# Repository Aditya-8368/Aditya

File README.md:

# stage-1------------------------------------------------------------<br>

# problem-1 : Design a schematic of circuit controlling a servo motor using a potentiometer. Also Simulate the circuit on tinkercad

link to tinker cad for my project of stage-1 (https://www.tinkercad.com/things/lVUwzbY1CdB-stage-1)

code of Arduino:

#include <Servo.h>

int val = 0;

int servo = 0;

int outval = 0;

Servo servo_9;

void setup()
{
  pinMode(A1, INPUT);
  servo_9.attach(9, 500, 2500);
  pinMode(LED_BUILTIN, OUTPUT);
}

void loop()
{
  val = analogRead(A1);
  outval = map(val, 0, 1023, 0, 180);
  servo_9.write(outval);

  digitalWrite(LED_BUILTIN, HIGH);
  delay(10); // Delay a little bit to improve simulation performance
}

# stage-2------------------------------------------------------------<br>

# problem-1 : Controlling LED intensity using PWM registers directly. (without using analogWrite/digitalWrite function)

this is a link for my tinkercad file for stage-2 problem-1 (https://www.tinkercad.com/things/dcMnIvQHpTa-magnificent-amberis)

Arduino code :

// C++ code

const int ledPin = 9;

void setup() {
  
  pinMode(ledPin, OUTPUT);

  TCCR1A |= (1 << WGM11) | (1 << COM1A1);
  TCCR1B |= (1 << WGM12) | (1 << WGM13) | (1 << CS10);

  OCR1A = 255;

  OCR1B = 0;
}

void loop() {
  
  for (int brightness = 0; brightness <= 255; brightness++) {
    OCR1B = brightness;
    delay(10);
  }

  for (int brightness = 255; brightness >= 0; brightness--) {
    OCR1B = brightness;
    delay(10);
  }
}

# problem-2 : Sweep a servo without using the Servo library controlled with IR remote. (Press 1 for right sweep ie from 0 to 180 degree and 2 for reverse)

this is a link for my tinkercad file for stage-2 problem-2 (https://www.tinkercad.com/things/60p1n9k2j1E-sizzling-blad)

Arduino code :
# NOTE : This code is not working in tinkercad dut to "IRRemote configuration of buttons" but compilation is going well and it will run on another remote or hardware

#include <IRremote.h>

#define IR_PIN 11 
#define SERVO_PIN 9

IRrecv irrecv(IR_PIN);
decode_results results;

int servoPos = 0;

void setup() {
  pinMode(SERVO_PIN, OUTPUT);
  irrecv.enableIRIn();
}

void loop() {
  if (irrecv.decode(&results)) {
    if (results.value == 0xFF30CF) { 
      sweepServo(0, 180, 1);
    } else if (results.value == 0xFF18E7) { 
      sweepServo(180, 0, -1);
    }
    irrecv.resume();
  }
}

void sweepServo(int from, int to, int step) {
  for (int i = from; i != to; i += step) {
    servoPos = i;
    updateServo();
    delay(15);
  }
}

void updateServo() {
  
  int pulseWidth = map(servoPos, 0, 180, 500, 2500);
  
  digitalWrite(SERVO_PIN, HIGH);
  delayMicroseconds(pulseWidth);
  digitalWrite(SERVO_PIN, LOW);
}

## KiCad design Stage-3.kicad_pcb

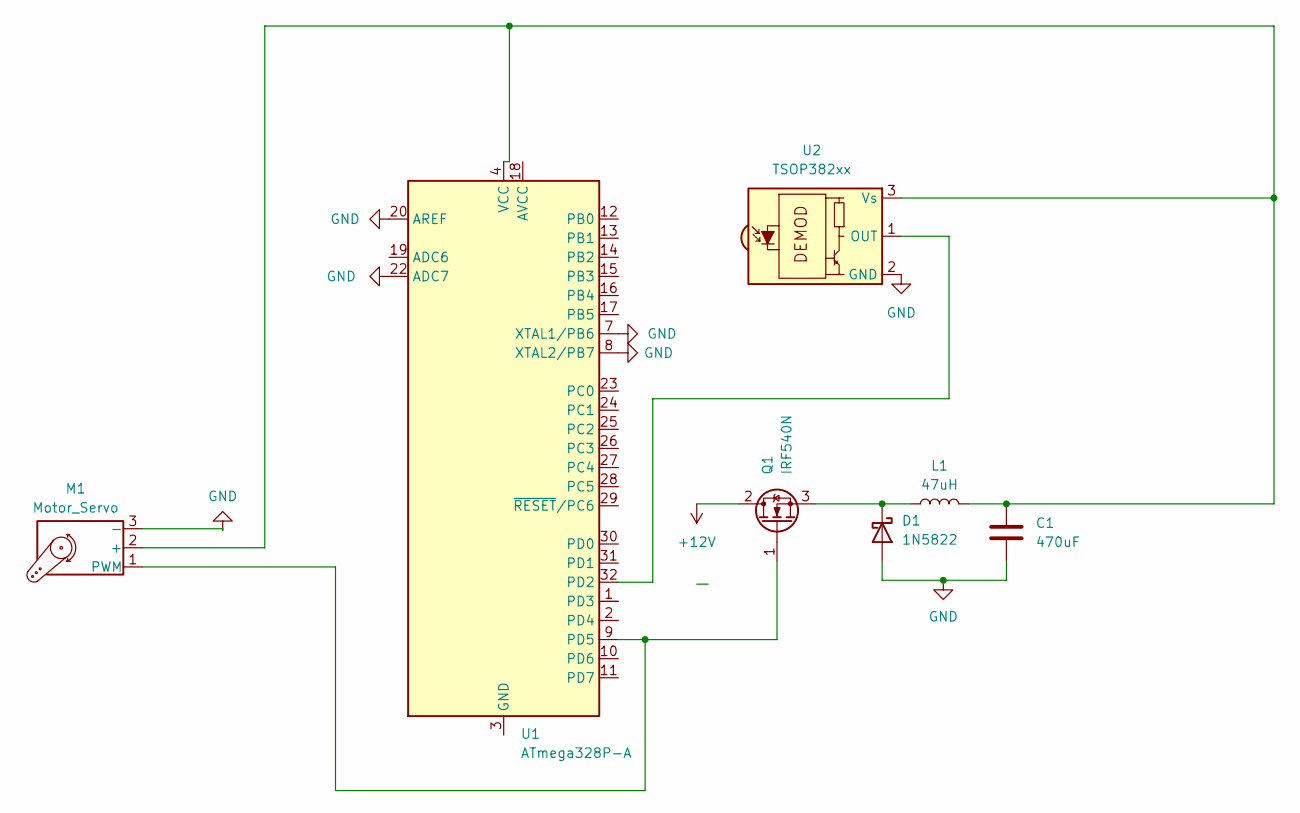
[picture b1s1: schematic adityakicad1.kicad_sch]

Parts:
C1: 470uF; CP_Elec_3x5.3
D1: 1N5822; D_DO-201AD_P15.24mm_Horizontal
L1: 47uH; L_6.3x6.3_H3
M1: Motor_Servo; JST_ZE_B05B-ZESK-D_1x05_P1.50mm_Vertical
Q1: IRF540N; TO-220-3_Vertical
U1: ATmega328P-A; TQFP-32_7x7mm_P0.8mm
U2: TSOP382xx; Vishay_MINICAST-3Pin

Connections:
+12V: Q1.2 (D)
GND: C1.2, D1.2 (A), M1.3 (-), U1.7 (XTAL1/PB6), U1.8 (XTAL2/PB7), U1.20 (AREF), U1.22 (ADC7), U2.2 (GND)
unnamed: D1.1 (K), L1.1, Q1.3 (S)
unnamed: C1.1, L1.2, M1.2 (+), U1.4 (VCC), U1.6 (VCC), U2.3 (Vs)
unnamed: M1.1 (PWM), Q1.1 (G), U1.9 (PD5)
unnamed: U1.3 (GND), U1.5 (GND), U1.21 (GND)
unnamed: U1.32 (PD2), U2.1 (OUT)

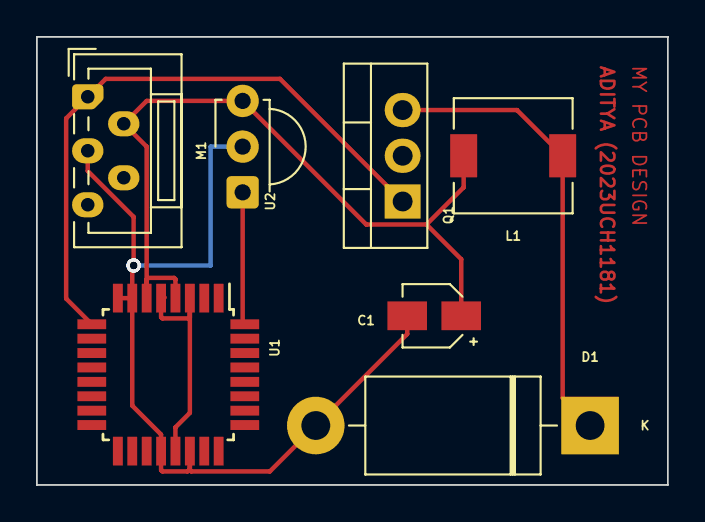
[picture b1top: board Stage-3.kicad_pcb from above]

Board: 2 copper layers, 35.1 x 24.9 mm, 7 parts (0 on the bottom side), 6 nets.

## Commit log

2024-01-28 added tinkercad link and arduino code for stage-1 project
2024-01-29 creating new file for stage-2
2024-01-29 creating new file for stage-3
2024-01-29 editing
2024-01-29 mention link of tinkercad and Arduino code for stage-2
2024-01-29 updating
2024-01-30 merging all projects
2024-01-30 removed README1.md , README2.md
2024-01-30 added stage-2 problem-2
2024-01-31 adding KICAD pcb editor and pcb schemetic files
2024-01-31 deleted
2024-01-31 uploading
2024-01-31 edit
2024-01-31 edited name
2024-02-01 uploded screenshot of pcb and schemetics
2024-02-01 uploded pdf of schemetic of stage-3
2024-02-01 changed name of file
2024-02-02 updated stage-2 code
